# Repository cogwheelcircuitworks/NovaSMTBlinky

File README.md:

# NovaSMTBlinky

ATtiny-based, Surface-mount, 5x7 LED dot-matrix display board used in classes

More description over on https://hackaday.io/project/7788-nova-smt-blinky 

It has also been known to be for sale on Tindie: https://www.tindie.com/products/bcoggs/nova-smt-blinky--hackable-5x7-dot-matrix-/

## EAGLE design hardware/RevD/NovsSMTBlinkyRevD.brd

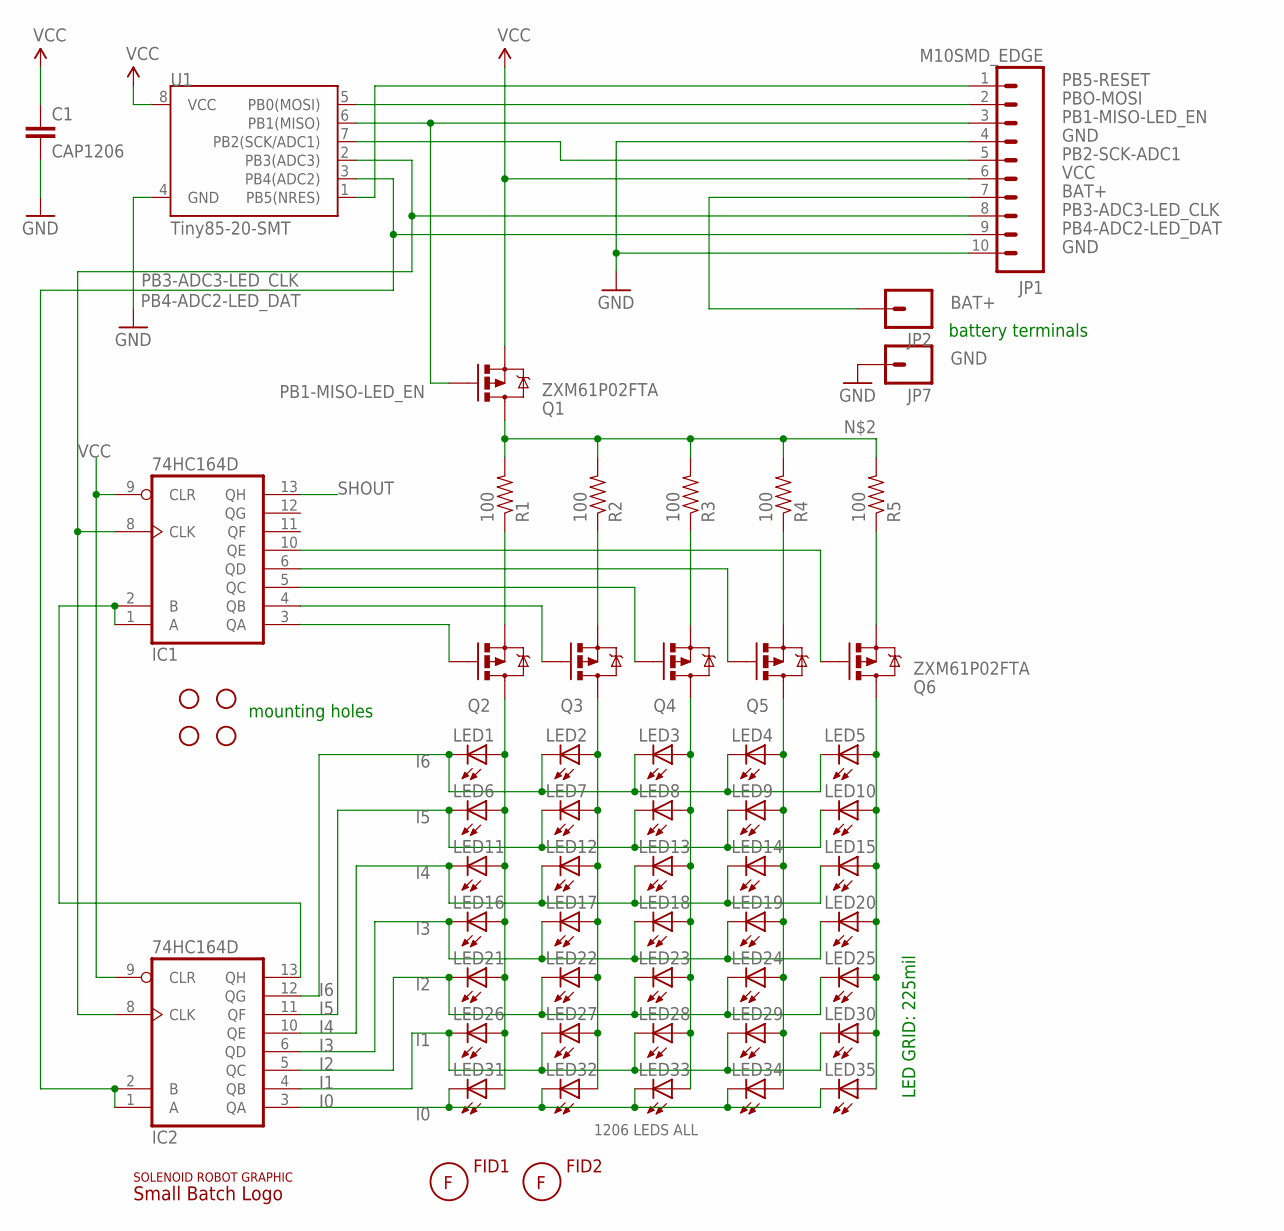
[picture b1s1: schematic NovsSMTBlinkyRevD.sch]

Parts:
C1: CAP1206; 1206
FID1, FID2: FIDUCIAL; FID05MM
IC1, IC2: 74HC164D; SO14
JP1: M10SMD_EDGE; 1X10_SMD_EDGE
JP2, JP7: M01NOSILK-KIT; 1X01NS-KIT
JP3, JP4, JP5, JP6: MTGHOLE110MIL; HOLE112
LED1, LED2, LED3, LED4, LED5, LED6, LED7, LED8, LED9, LED10, LED11, LED12, LED13, LED14, LED15, LED16, LED17, LED18, LED19, LED20, LED21, LED22, LED23, LED24, LED25, LED26, LED27, LED28, LED29, LED30, LED31, LED32, LED33, LED34, LED35: LED1206; LED-1206
Q1, Q6: ZXM61P02FTA; SOT23-3
Q2, Q3, Q4, Q5: MOSFET-PCHANNELSMD; SOT23-3
R1, R2, R3, R4, R5: 100; 1206
U1: Tiny85-20-SMT; SO08-EIAJ
U$1: SOLENOID_ROBOT; SOLENOID_ROBT_450MIL
U$4: SMALLBATCH_LOGO750W; SMALLBATCH_750W

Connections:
BAT+: JP1.7, JP2.1
GND: C1.2, IC1.7 (GND), IC2.7 (GND), JP1.4, JP1.10, JP7.1, U1.4 (GND)
I0: IC2.3 (QA), LED31.C, LED32.C, LED33.C, LED34.C, LED35.C
I1: IC2.4 (QB), LED26.C, LED27.C, LED28.C, LED29.C, LED30.C
I2: IC2.5 (QC), LED21.C, LED22.C, LED23.C, LED24.C, LED25.C
I3: IC2.6 (QD), LED16.C, LED17.C, LED18.C, LED19.C, LED20.C
I4: IC2.10 (QE), LED11.C, LED12.C, LED13.C, LED14.C, LED15.C
I5: IC2.11 (QF), LED6.C, LED7.C, LED8.C, LED9.C, LED10.C
I6: IC2.12 (QG), LED1.C, LED2.C, LED3.C, LED4.C, LED5.C
unnamed: IC1.1 (A), IC1.2 (B), IC2.13 (QH)
unnamed: Q1.3 (D), R1.2, R2.2, R3.2, R4.2, R5.2
unnamed: LED1.A, LED6.A, LED11.A, LED16.A, LED21.A, LED26.A, LED31.A, Q2.3 (D)
unnamed: LED2.A, LED7.A, LED12.A, LED17.A, LED22.A, LED27.A, LED32.A, Q3.3 (D)
unnamed: LED4.A, LED9.A, LED14.A, LED19.A, LED24.A, LED29.A, LED34.A, Q5.3 (D)
unnamed: LED5.A, LED10.A, LED15.A, LED20.A, LED25.A, LED30.A, LED35.A, Q6.3 (D)
unnamed: LED3.A, LED8.A, LED13.A, LED18.A, LED23.A, LED28.A, LED33.A, Q4.3 (D)
unnamed: Q2.2 (S), R1.1
unnamed: Q3.2 (S), R2.1
unnamed: Q4.2 (S), R3.1
unnamed: Q5.2 (S), R4.1
unnamed: Q6.2 (S), R5.1
unnamed: IC1.3 (QA), Q2.1 (G)
unnamed: IC1.4 (QB), Q3.1 (G)
unnamed: IC1.5 (QC), Q4.1 (G)
unnamed: IC1.6 (QD), Q5.1 (G)
unnamed: IC1.10 (QE), Q6.1 (G)
PB1-MISO-LED_EN: JP1.3, Q1.1 (G), U1.6 (PB1(MISO))
PB2-SCK-ADC1: JP1.5, U1.7 (PB2(SCK/ADC1))
PB3-ADC3-LED_CLK: IC1.8 (CLK), IC2.8 (CLK), JP1.8, U1.2 (PB3(ADC3))
PB4-ADC2-LED_DAT: IC2.1 (A), IC2.2 (B), JP1.9, U1.3 (PB4(ADC2))
PB5-RESET: JP1.1, U1.1 (PB5(NRES))
PBO-MOSI: JP1.2, U1.5 (PB0(MOSI))
SHOUT: IC1.13 (QH)
VCC: C1.1, IC1.9 (CLR), IC1.14 (VCC), IC2.9 (CLR), IC2.14 (VCC), JP1.6, Q1.2 (S), U1.8 (VCC)

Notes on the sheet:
1206 LEDS ALL
mounting holes
LED GRID: 225mil
battery terminals

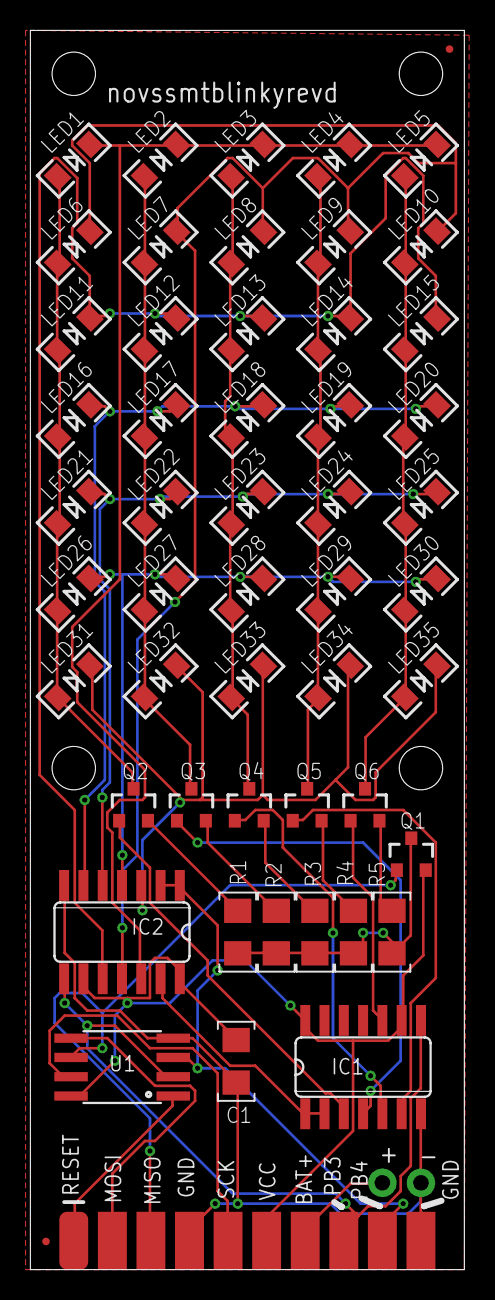
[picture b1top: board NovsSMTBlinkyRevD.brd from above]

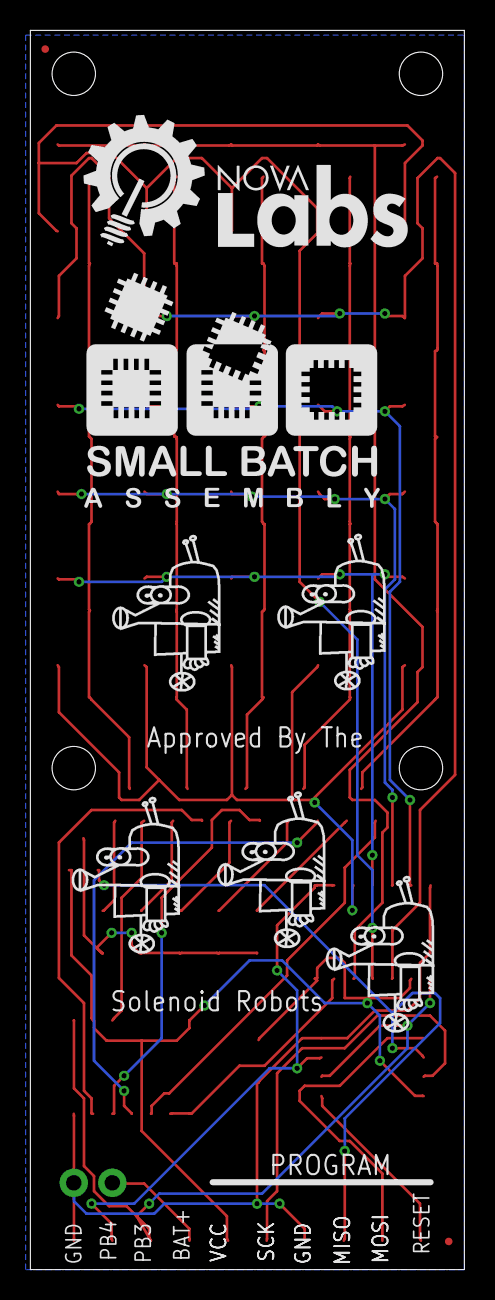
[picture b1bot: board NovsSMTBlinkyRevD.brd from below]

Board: 2 copper layers, 28.6 x 81.6 mm, 66 parts (7 on the bottom side), 33 nets.

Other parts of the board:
U$2: NOVA-LABS-LOGO-FULL-SMALL
U$3, U$5, U$6, U$7: SOLENOID_ROBOT; SOLENOID_ROBT_450MIL

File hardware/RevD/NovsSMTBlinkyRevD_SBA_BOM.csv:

##########################################################################
       Name: Placement Bill of Materials Generator

    Version: 4 (2-sided, top)
         By: Small Batch Assembly
        URL: www.smallbatchassembly.com
 SourceFile: NovsSMTBlinkyRevD.brd
   DateTime: 8/1/2016 8:48 AM
      Units: inches
##########################################################################
REF,PACKAGE,VALUE,X,Y,ROTATION,
C1   , 1206            , CAP1206     , 0.6460, 0.5900, 270.0
FID1   , FID05MM            ,      , 0.1530, 0.1230, 0.0
FID2   , FID05MM            ,      , 1.1990, 3.2140, 0.0
IC1   , SO14            , 74HC164D     , 0.9750, 0.5750, 0.0
IC2   , SO14            , 74HC164D     , 0.3500, 0.9250, 180.0
JP1   , 1X10_SMD_EDGE            , M10SMD_EDGE     , 0.6750, 0.1250, 0.0
LED1   , LED-1206            ,      , 0.2250, 2.9250, 45.0
LED2   , LED-1206            ,      , 0.4500, 2.9250, 45.0
LED3   , LED-1206            ,      , 0.6750, 2.9250, 45.0
LED4   , LED-1206            ,      , 0.9000, 2.9250, 45.0
LED5   , LED-1206            ,      , 1.1250, 2.9250, 45.0
LED6   , LED-1206            ,      , 0.2250, 2.7000, 45.0
LED7   , LED-1206            ,      , 0.4500, 2.7000, 45.0
LED8   , LED-1206            ,      , 0.6750, 2.7000, 45.0
LED9   , LED-1206            ,      , 0.9000, 2.7000, 45.0
LED10   , LED-1206            ,      , 1.1250, 2.7000, 45.0
LED11   , LED-1206            ,      , 0.2250, 2.4750, 45.0
LED12   , LED-1206            ,      , 0.4500, 2.4750, 45.0
LED13   , LED-1206            ,      , 0.6750, 2.4750, 45.0
LED14   , LED-1206            ,      , 0.9000, 2.4750, 45.0
LED15   , LED-1206            ,      , 1.1250, 2.4750, 45.0
LED16   , LED-1206            ,      , 0.2250, 2.2500, 45.0
LED17   , LED-1206            ,      , 0.4500, 2.2500, 45.0
LED18   , LED-1206            ,      , 0.6750, 2.2500, 45.0
LED19   , LED-1206            ,      , 0.9000, 2.2500, 45.0
LED20   , LED-1206            ,      , 1.1250, 2.2500, 45.0
LED21   , LED-1206            ,      , 0.2250, 2.0250, 45.0
LED22   , LED-1206            ,      , 0.4500, 2.0250, 45.0
LED23   , LED-1206            ,      , 0.6750, 2.0250, 45.0
LED24   , LED-1206            ,      , 0.9000, 2.0250, 45.0
LED25   , LED-1206            ,      , 1.1250, 2.0250, 45.0
LED26   , LED-1206            ,      , 0.2250, 1.8000, 45.0
LED27   , LED-1206            ,      , 0.4500, 1.8000, 45.0
LED28   , LED-1206            ,      , 0.6750, 1.8000, 45.0
LED29   , LED-1206            ,      , 0.9000, 1.8000, 45.0
LED30   , LED-1206            ,      , 1.1250, 1.8000, 45.0
LED31   , LED-1206            ,      , 0.2250, 1.5750, 45.0
LED32   , LED-1206            ,      , 0.4500, 1.5750, 45.0
LED33   , LED-1206            ,      , 0.6750, 1.5750, 45.0
LED34   , LED-1206            ,      , 0.9000, 1.5750, 45.0
LED35   , LED-1206            ,      , 1.1250, 1.5750, 45.0
Q1   , SOT23-3            , ZXM61P02FTA     , 1.1000, 1.1250, 0.0
Q2   , SOT23-3            , MOSFET-PCHANNELSMD     , 0.3800, 1.2530, 0.0
Q3   , SOT23-3            , MOSFET-PCHANNELSMD     , 0.5300, 1.2530, 0.0
Q4   , SOT23-3            , MOSFET-PCHANNELSMD     , 0.6800, 1.2530, 0.0
Q5   , SOT23-3            , MOSFET-PCHANNELSMD     , 0.8300, 1.2530, 0.0
Q6   , SOT23-3            , ZXM61P02FTA     , 0.9800, 1.2530, 0.0
R1   , 1206            , 100     , 0.6500, 0.9250, 270.0
R2   , 1206            , 100     , 0.7500, 0.9250, 270.0
R3   , 1206            , 100     , 0.8500, 0.9250, 270.0
R4   , 1206            , 100     , 0.9500, 0.9250, 270.0
R5   , 1206            , 100     , 1.0500, 0.9250, 270.0
U1   , SO08-EIAJ            , Tiny85-20-SMT     , 0.3500, 0.5750, 90.0

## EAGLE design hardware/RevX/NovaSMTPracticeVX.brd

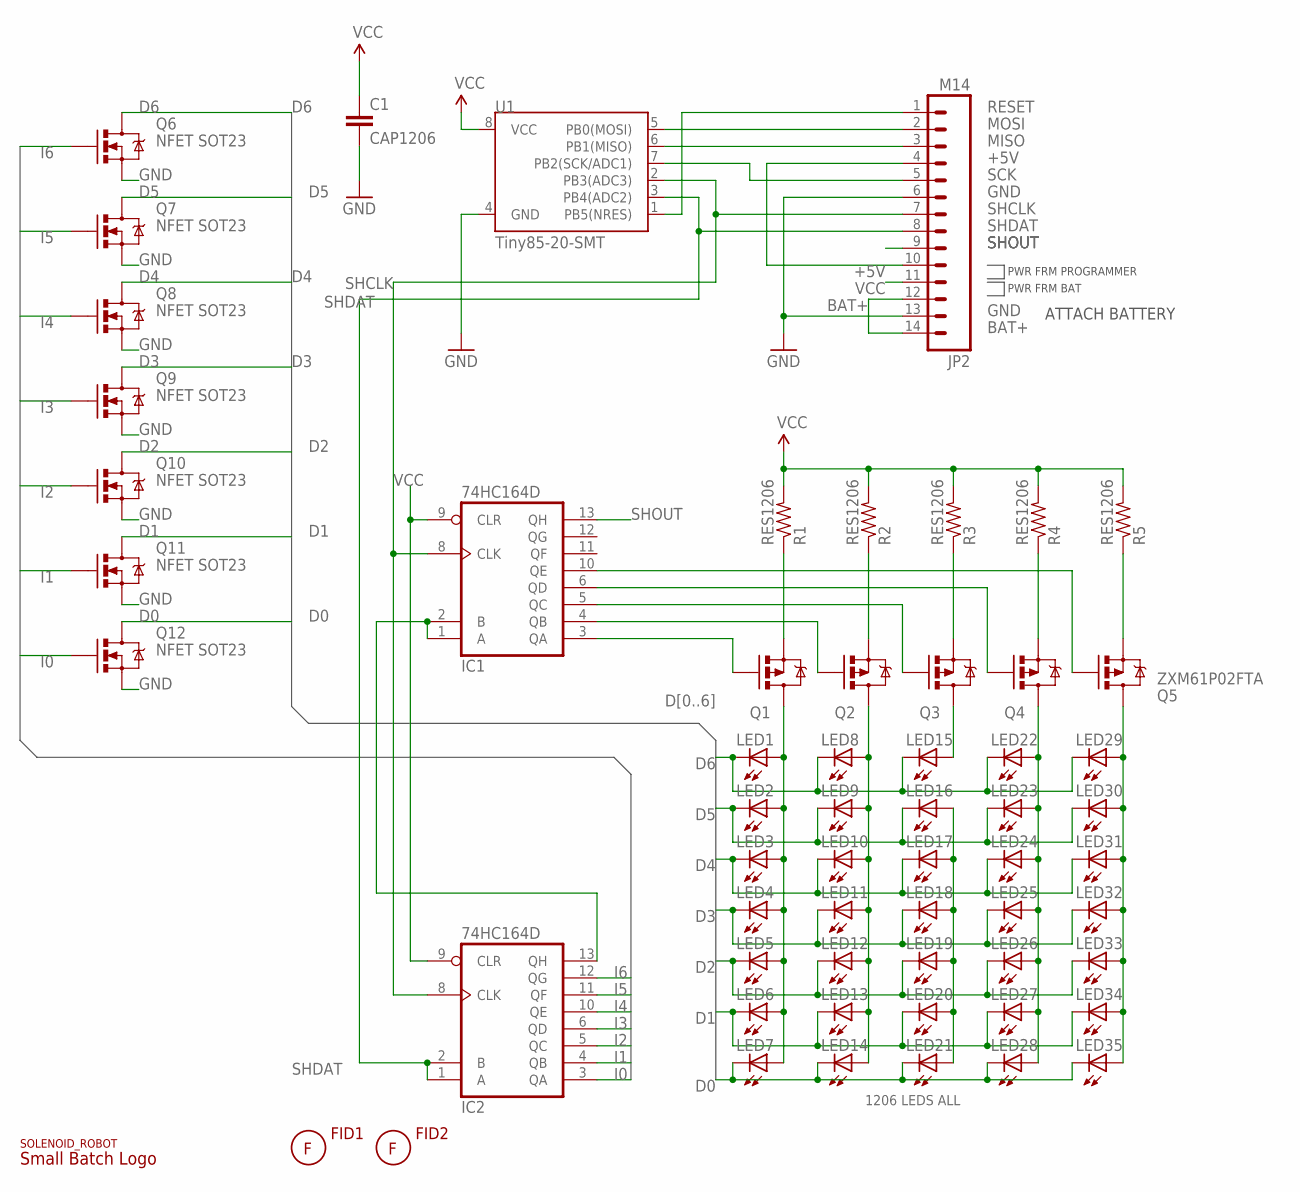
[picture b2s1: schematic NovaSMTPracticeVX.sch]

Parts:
C1: CAP1206; 1206
FID1, FID2: FIDUCIAL; FID05MM
IC1, IC2: 74HC164D; SO14
JP2: M14; 1X14_SMTPADS
LED1, LED2, LED3, LED4, LED5, LED6, LED7, LED8, LED9, LED10, LED11, LED12, LED13, LED14, LED15, LED16, LED17, LED18, LED19, LED20, LED21, LED22, LED23, LED24, LED25, LED26, LED27, LED28, LED29, LED30, LED31, LED32, LED33, LED34, LED35: LED1206; LED-1206
Q1, Q2, Q3, Q4: MOSFET-PCHANNELSMD; SOT23-3
Q5: ZXM61P02FTA; SOT23-3
Q6, Q7, Q8, Q9, Q10, Q11, Q12: NFET SOT23; SOT23-3
R1, R2, R3, R4, R5: RES1206; 1206
U1: Tiny85-20-SMT; SO08-EIAJ
U$1: SOLENOID_ROBOT; SOLENOID_ROBT_450MIL
U$4: SMALLBATCH_LOGO750W; SMALLBATCH_750W

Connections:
+5V: JP2.4, JP2.10
BAT+: JP2.12, JP2.14
D0: LED7.C, LED14.C, LED21.C, LED28.C, LED35.C, Q12.3 (D)
D1: LED6.C, LED13.C, LED20.C, LED27.C, LED34.C, Q11.3 (D)
D2: LED5.C, LED12.C, LED19.C, LED26.C, LED33.C, Q10.3 (D)
D3: LED4.C, LED11.C, LED18.C, LED25.C, LED32.C, Q9.3 (D)
D4: LED3.C, LED10.C, LED17.C, LED24.C, LED31.C, Q8.3 (D)
D5: LED2.C, LED9.C, LED16.C, LED23.C, LED30.C, Q7.3 (D)
D6: LED1.C, LED8.C, LED15.C, LED22.C, LED29.C, Q6.3 (D)
GND: C1.2, IC1.7 (GND), IC2.7 (GND), JP2.6, JP2.13, Q6.2 (S), Q7.2 (S), Q8.2 (S), Q9.2 (S), Q10.2 (S), Q11.2 (S), Q12.2 (S), U1.4 (GND)
I0: IC2.3 (QA), Q12.1 (G)
I1: IC2.4 (QB), Q11.1 (G)
I2: IC2.5 (QC), Q10.1 (G)
I3: IC2.6 (QD), Q9.1 (G)
I4: IC2.10 (QE), Q8.1 (G)
I5: IC2.11 (QF), Q7.1 (G)
I6: IC2.12 (QG), Q6.1 (G)
MISO: JP2.3, U1.6 (PB1(MISO))
MOSI: JP2.2, U1.5 (PB0(MOSI))
unnamed: IC1.1 (A), IC1.2 (B), IC2.13 (QH)
unnamed: LED1.A, LED2.A, LED3.A, LED4.A, LED5.A, LED6.A, LED7.A, Q1.3 (D)
unnamed: LED8.A, LED9.A, LED10.A, LED11.A, LED12.A, LED13.A, LED14.A, Q2.3 (D)
unnamed: LED16.A, LED17.A, LED18.A, LED19.A, LED20.A, LED21.A
unnamed: LED22.A, LED23.A, LED24.A, LED25.A, LED26.A, LED27.A, LED28.A, Q4.3 (D)
unnamed: LED29.A, LED30.A, LED31.A, LED32.A, LED33.A, LED34.A, LED35.A, Q5.3 (D)
unnamed: LED15.A, Q3.3 (D)
unnamed: Q1.2 (S), R1.1
unnamed: Q2.2 (S), R2.1
unnamed: Q3.2 (S), R3.1
unnamed: Q4.2 (S), R4.1
unnamed: Q5.2 (S), R5.1
unnamed: IC1.3 (QA), Q1.1 (G)
unnamed: IC1.4 (QB), Q2.1 (G)
unnamed: IC1.5 (QC), Q3.1 (G)
unnamed: IC1.6 (QD), Q4.1 (G)
unnamed: IC1.10 (QE), Q5.1 (G)
RESET: JP2.1, U1.1 (PB5(NRES))
SCK: JP2.5, U1.7 (PB2(SCK/ADC1))
SHCLK: IC1.8 (CLK), IC2.8 (CLK), JP2.7, U1.2 (PB3(ADC3))
SHDAT: IC2.1 (A), IC2.2 (B), JP2.8, U1.3 (PB4(ADC2))
SHOUT: IC1.13 (QH), JP2.9
VCC: C1.1, IC1.9 (CLR), IC1.14 (VCC), IC2.9 (CLR), IC2.14 (VCC), JP2.11, R1.2, R2.2, R3.2, R4.2, R5.2, U1.8 (VCC)

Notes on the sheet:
ATTACH BATTERY
1206 LEDS ALL
PWR FRM PROGRAMMER
PWR FRM BAT

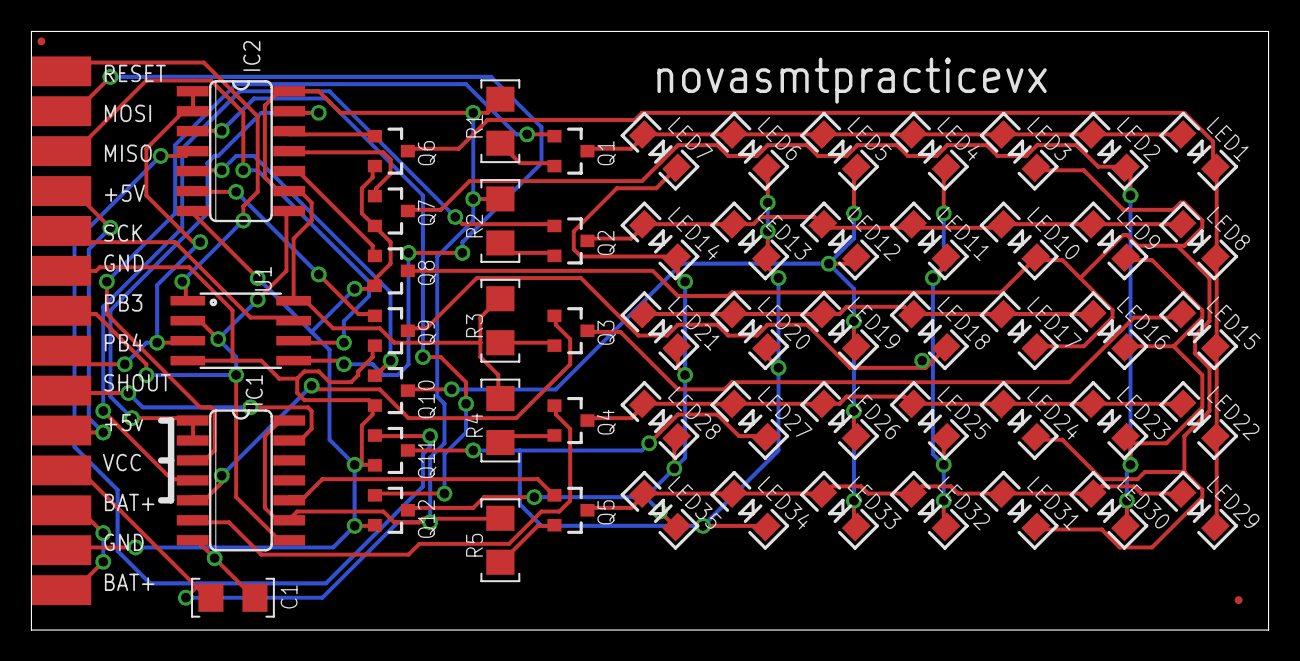
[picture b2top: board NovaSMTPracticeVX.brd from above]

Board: 2 copper layers, 78.7 x 38.1 mm, 66 parts (7 on the bottom side), 42 nets.

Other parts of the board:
U$2: NOVA-LABS-LOGO-FULL-SMALL
U$3, U$5, U$6, U$7: SOLENOID_ROBOT; SOLENOID_ROBT_450MIL

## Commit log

2015-09-21 updated:README.md
2015-09-21 updated: /hardware/RevX/NovaSMTBlinkyRevX.gif
2015-09-21 new file: hardware/RevX/NovaSMTBlinkyRevX.gif
2015-09-21 modified: hardware/RevX/NovaSMTBlinkyRevX.gif
2015-09-22 new file: hardware/RevX/NovaSMTPracticeErrata.doc new file: hardware/RevX/NovaSMTPracticeVX-BOM.pdf new file: hardware/RevX/NovaSMTPracticeVX-sch.pdf new file: hardware/RevX/NovaSMTPracticeVX.brd new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
2015-09-22 deleted: hardware/RevX/NovaSMTPracticeErrata.doc new file: hardware/RevX/NovaSMTPracticeErrata.pdf
2015-09-22 deleted: hardware/RevX/NovaSMTPracticeVX.pdf
2015-09-22 new file: hardware/RevX/NovaSMTPracticeRevA-brd.pdf new file: hardware/RevX/NovaSMTPracticeVX-Fab/NovaSMTPracticeVX.boardoutline.ger new file: hardware/RevX/NovaSMTPracticeVX-Fab/NovaSMTPracticeVX.bo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
2015-09-22 new file: software/hardware/attiny/avr/boards.txt new file: software/hardware/attiny/avr/platform.txt new file: software/hardware/attiny/avr/variants/tiny14/pins_arduino.h new file: software/hardware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
2015-09-22 Created README.md
2015-09-22 new file: hardware/RevX/eagleUp_NovaSMTPracticeVX_board_bottom.png new file: hardware/RevX/eagleUp_NovaSMTPracticeVX_board_top.png
2015-09-22 new file: hardware/RevX/NovaSMTBlinkyRevX_1.gif
2015-09-22 modified: README.md
2016-07-31 Major revsion
    deleted: software/hardware/attiny/avr/boards.txt
    deleted: software/hardware/attiny/avr/platform.txt
    deleted: software/hardware/attiny/avr/variants/tiny14/pins_arduino.h
    deleted: software/hardware/attiny/avr/variants/tiny8/pins_arduino.h
    deleted: software/libraries/ATtinyTimer/ATtinyTimer.cpp
    deleted: software/libraries/ATtinyTimer/ATtinyTimer.h
2016-07-31 new file: software/libraries/NovaDotMatrix/ATtinyTimer.cpp new file: software/libraries/NovaDotMatrix/ATtinyTimer.h new file: software/libraries/NovaDotMatrix/FontAlphaNum35.h new file: software/libr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
2016-07-31 deleted: fixfont.py
2016-07-31 modified: ../../README.md deleted: readme.md
2016-07-31 new file: NovaDotMatrixDriver/NovaDotMatrixCommands.h new file: NovaDotMatrixDriver/NovaDotMatrixDriver.cpp new file: NovaDotMatrixDriver/NovaDotMatrixDriver.h new file: NovaDotMatrixDriver/examples/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
2016-07-31 deleted: sketches/NovaSMTBlinky/NovaSMTBlinky.ino
2016-07-31 new file: README.md
2016-08-01 new file: etc/animated.gif
2016-08-01 new file: etc/board_top.png
2016-08-01 modified: etc/board_top.png
2016-08-01 new file: etc/hookup.png
2016-08-01 new file: RevD/NovaSMTBlinkyRevD.xls renamed: RevX/NovaSMTPracticeVX.brd -> RevD/NovsSMTBlinkyRevD.brd renamed: RevX/NovaSMTPracticeVX.sch -> RevD/NovsSMTBlinkyRevD.sch new file: RevD/NovsSMTBlinkyRe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
2016-08-01 new file: RevD/NovsSMTBlinkyRevD_BRD.pdf
2016-08-02 deleted: NovaSMTBlinkyRevD.xls deleted: NovsSMTBlinkyRevD_SBA_BOM.csv
2016-08-02 NovsSMTBlinkyRevD_BOM.pdf
2017-03-17 Changes to be committed: new file: doc/NovaBlinky.odt new file: doc/NovaBlinky.pdf
2017-03-17 committed by mistake
2017-04-03 new file: etc/2017-04-01 07.09.22.gif new file: etc/2017-04-01 07.12.12.gif new file: etc/2017-04-01 07.17.49.gif new file: etc/NovaSMTBlinkyArduinoHookup.png
2017-04-03 renamed: etc/2017-04-01 07.09.22.gif -> etc/animated2.gif renamed: etc/2017-04-01 07.12.12.gif -> etc/animated3.gif renamed: etc/2017-04-01 07.17.49.gif -> etc/animated4.gif
2017-04-03 Added Arduino Hookup d'gram to doc/NovaBlinky.odt, doc/NovaBlinky.pdf

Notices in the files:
parts and their libraries:
SparkFun-DiscreteSemi: Licensing: Creative Commons ShareAlike 4.0 International - https://creativecommons.org/licenses/by-sa/4.0
